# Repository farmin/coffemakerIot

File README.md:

# mokkamaster-autoff-iot

Simple project to demonstrate howto use Wifi and mqtt on a esp32 using the Arduino
framework. The project includes a custom sensor board that comunicates to host via
i2c. The sensor is ment to provide useful feedback from a MokkaMaster or similar type
of coffe machine.

## Installing

This project uses [Platformio](https://platformio.org/) as build platform. It installs from
terminal by typing in the following commands:
```
pip install platformio
cd ../coffemakerIot
platformio run
platformio run -t upload

```
### Prerequisites

You probably need pip to install platfomrio. you also need to add yourself to the dialout 
group.

```
python pip
sudo adduser $USER dialout
```

## Known bugs

I2c Bus dropouts, could be hw fault.
Wifi dropouts

# Investigate this
[E][ssl_client.cpp:32] handle_error(): UNKNOWN ERROR CODE (004E)
[E][ssl_client.cpp:34] handle_error(): MbedTLS message code: -78
[E][ssl_client.cpp:84] start_ssl_client(): Connect to Server failed!
[E][WiFiClientSecure.cpp:108] connect(): lwip_connect_r: 113
[E][ssl_client.cpp:84] start_ssl_client(): Connect to Server failed!
[E][WiFiClientSecure.cpp:108] connect(): lwip_connect_r: 113
[E][ssl_client.cpp:84] start_ssl_client(): Connect to Server failed!
[E][WiFiClientSecure.cpp:108] connect(): lwip_connect_r: 113

## Built With

* [Arduino](https://www.arduino.cc/) - Arduino enviroment
* [ArduinoJson](https://arduinojson.org/) - Json library
* [arduino-mqtt](https://github.com/256dpi/arduino-mqtt) - Mqtt framework
* [Adafruit-sensors](https://www.adafruit.com/) - libraries for ADS1X15 and MLX90614 sensors

## Authors

* **Armin Bårdseth** - *Initial work*

## License

This project is licensed under the MIT License - see the [LICENSE.md](LICENSE.md) file for details

## Acknowledgments

* Hat tip to anyone who's code was used
* Inspiration
* etc

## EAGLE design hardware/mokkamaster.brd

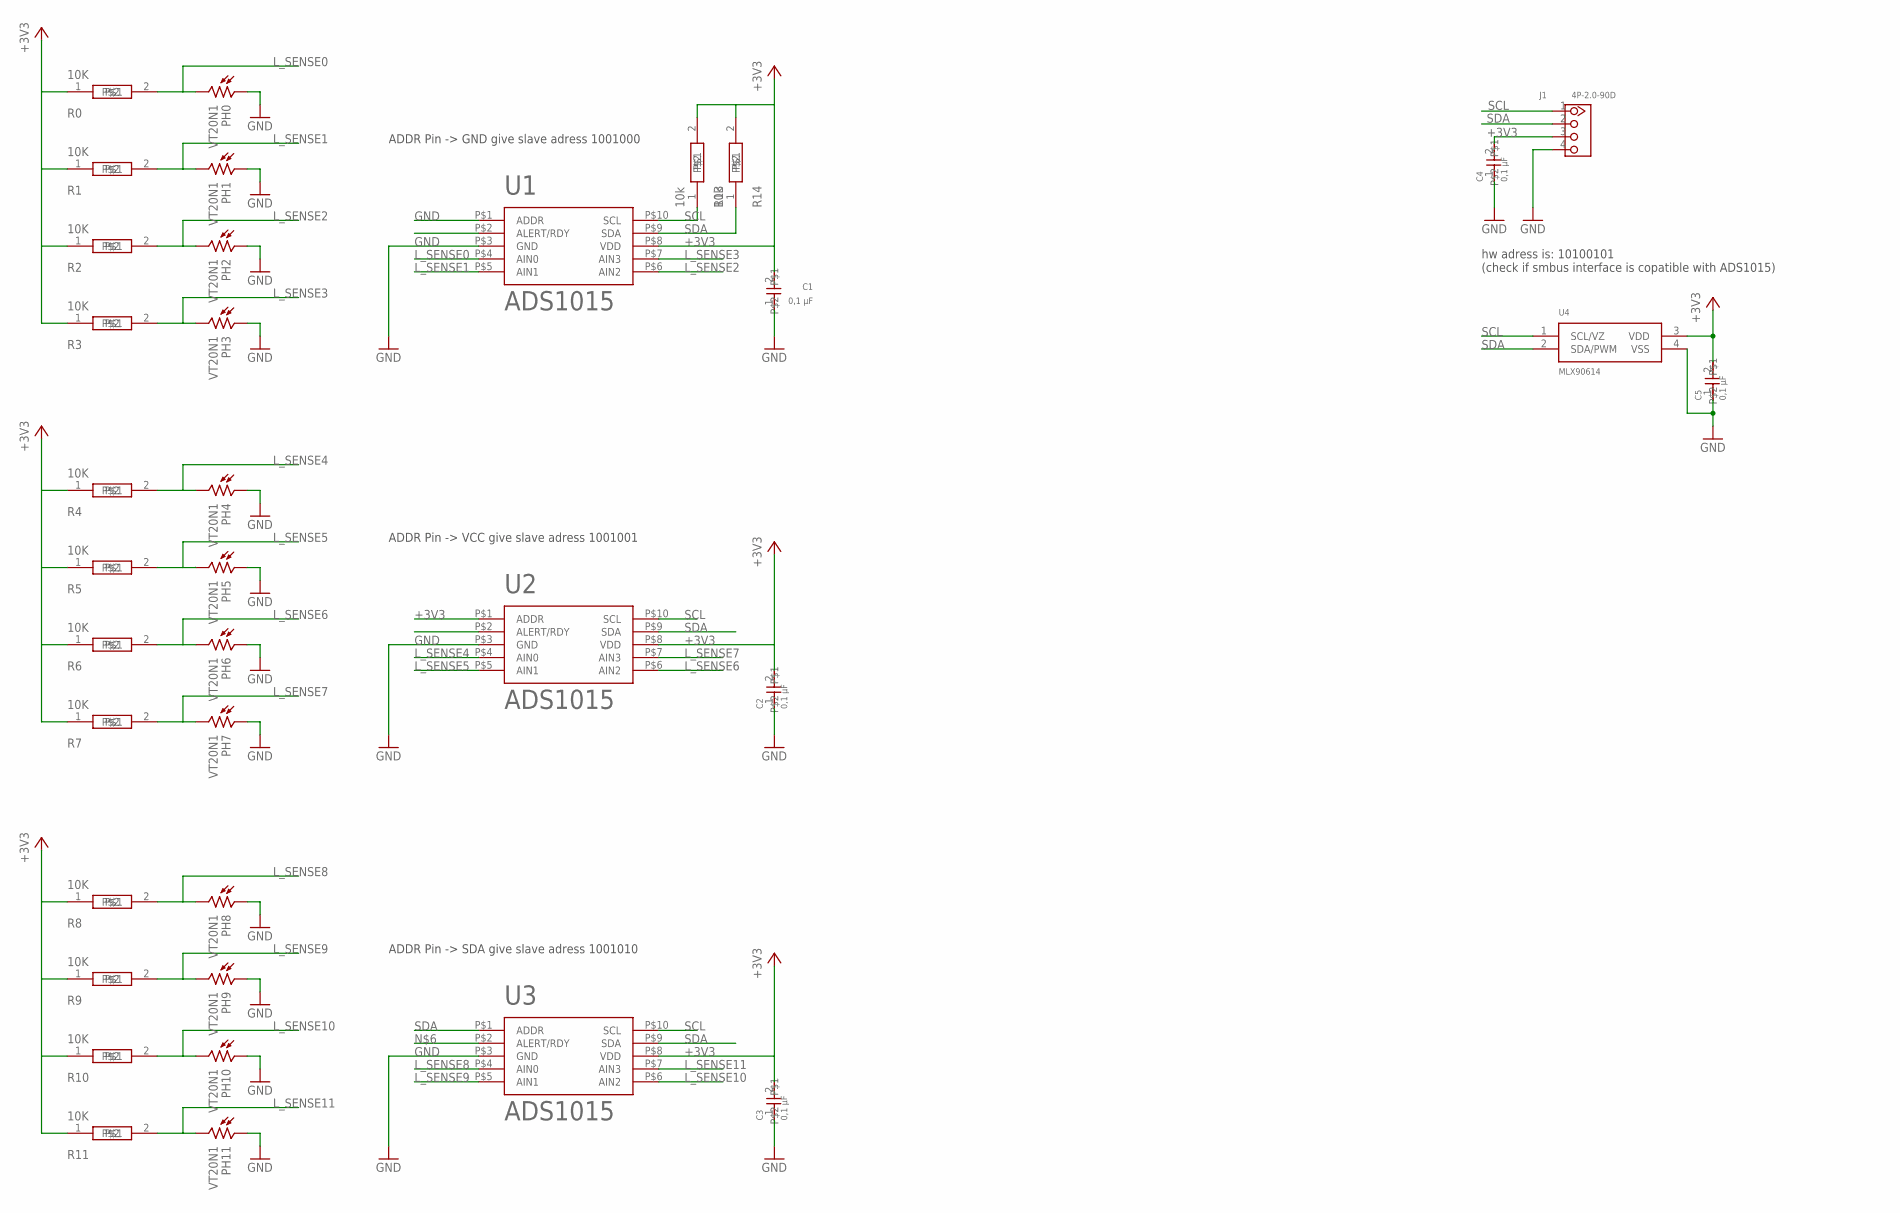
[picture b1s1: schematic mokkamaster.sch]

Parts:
C1, C2, C3, C4, C5: 0,1 µF; C0603
J1: 4P-2.0-90D; HW4-2.0-90D
PH0, PH1, PH2, PH3, PH4, PH5, PH6, PH7, PH8, PH9, PH10, PH11: VT20N1; TO46-VT200
R0, R1, R2, R3, R4, R5, R6, R7, R8, R9, R10, R11: 10K; R0603
R13, R14: 10k; R0603
U1, U2, U3: ADS1015; PDSO-G10
U4: MLX90614; SPARKFUN_TO-39

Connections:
+3V3: C1.2, C2.2, C3.2, C4.2, C5.2, J1.3, R0.1, R1.1, R2.1, R3.1, R4.1, R5.1, R6.1, R7.1, R8.1, R9.1, R10.1, R11.1, R13.2, R14.2, U1.P$8 (VDD), U2.P$1 (ADDR), U2.P$8 (VDD), U3.P$8 (VDD), U4.3 (VDD)
GND: C1.1, C2.1, C3.1, C4.1, C5.1, J1.4, PH0.1, PH1.1, PH2.1, PH3.1, PH4.1, PH5.1, PH6.1, PH7.1, PH8.1, PH9.1, PH10.1, PH11.1, U1.P$1 (ADDR), U1.P$3 (GND), U2.P$3 (GND), U3.P$3 (GND), U4.4 (VSS)
L_SENSE0: PH0.2, R0.2, U1.P$4 (AIN0)
L_SENSE1: PH1.2, R1.2, U1.P$5 (AIN1)
L_SENSE2: PH2.2, R2.2, U1.P$6 (AIN2)
L_SENSE3: PH3.2, R3.2, U1.P$7 (AIN3)
L_SENSE4: PH4.2, R4.2, U2.P$4 (AIN0)
L_SENSE5: PH5.2, R5.2, U2.P$5 (AIN1)
L_SENSE6: PH6.2, R6.2, U2.P$6 (AIN2)
L_SENSE7: PH7.2, R7.2, U2.P$7 (AIN3)
L_SENSE8: PH8.2, R8.2, U3.P$4 (AIN0)
L_SENSE9: PH9.2, R9.2, U3.P$5 (AIN1)
L_SENSE10: PH10.2, R10.2, U3.P$6 (AIN2)
L_SENSE11: PH11.2, R11.2, U3.P$7 (AIN3)
SCL: J1.1, R13.1, U1.P$10 (SCL), U2.P$10 (SCL), U3.P$10 (SCL), U4.1 (SCL/VZ)
SDA: J1.2, R14.1, U1.P$9 (SDA), U2.P$9 (SDA), U3.P$1 (ADDR), U3.P$9 (SDA), U4.2 (SDA/PWM)

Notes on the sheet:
ADDR Pin -> GND give slave adress 1001000
ADDR Pin -> VCC give slave adress 1001001
ADDR Pin -> SDA give slave adress 1001010
hw adress is: 10100101 (check if smbus interface is copatible with ADS1015)

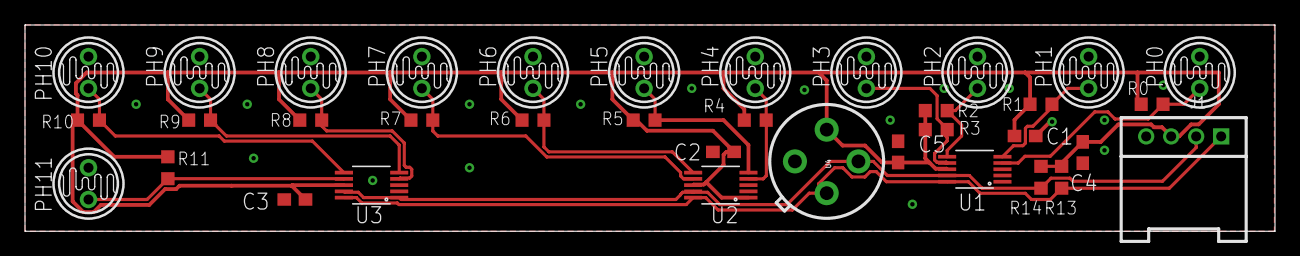
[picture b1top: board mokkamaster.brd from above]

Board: 2 copper layers, 100.0 x 16.5 mm, 36 parts (0 on the bottom side), 16 nets.

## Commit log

2018-05-08 moved to platformio build system, initial commit
2018-05-08 created hardware directory
2018-05-08 added shematic
2018-05-09 started config mode
2018-05-09 added hardware libraries
2018-05-09 config mode
2018-05-14 started on calibration
2018-05-24 updated dependencies
2018-05-24 refactoring
2018-05-24 added some comments
2018-05-25 Added some documentation, code cleaning. some changes to current sense
